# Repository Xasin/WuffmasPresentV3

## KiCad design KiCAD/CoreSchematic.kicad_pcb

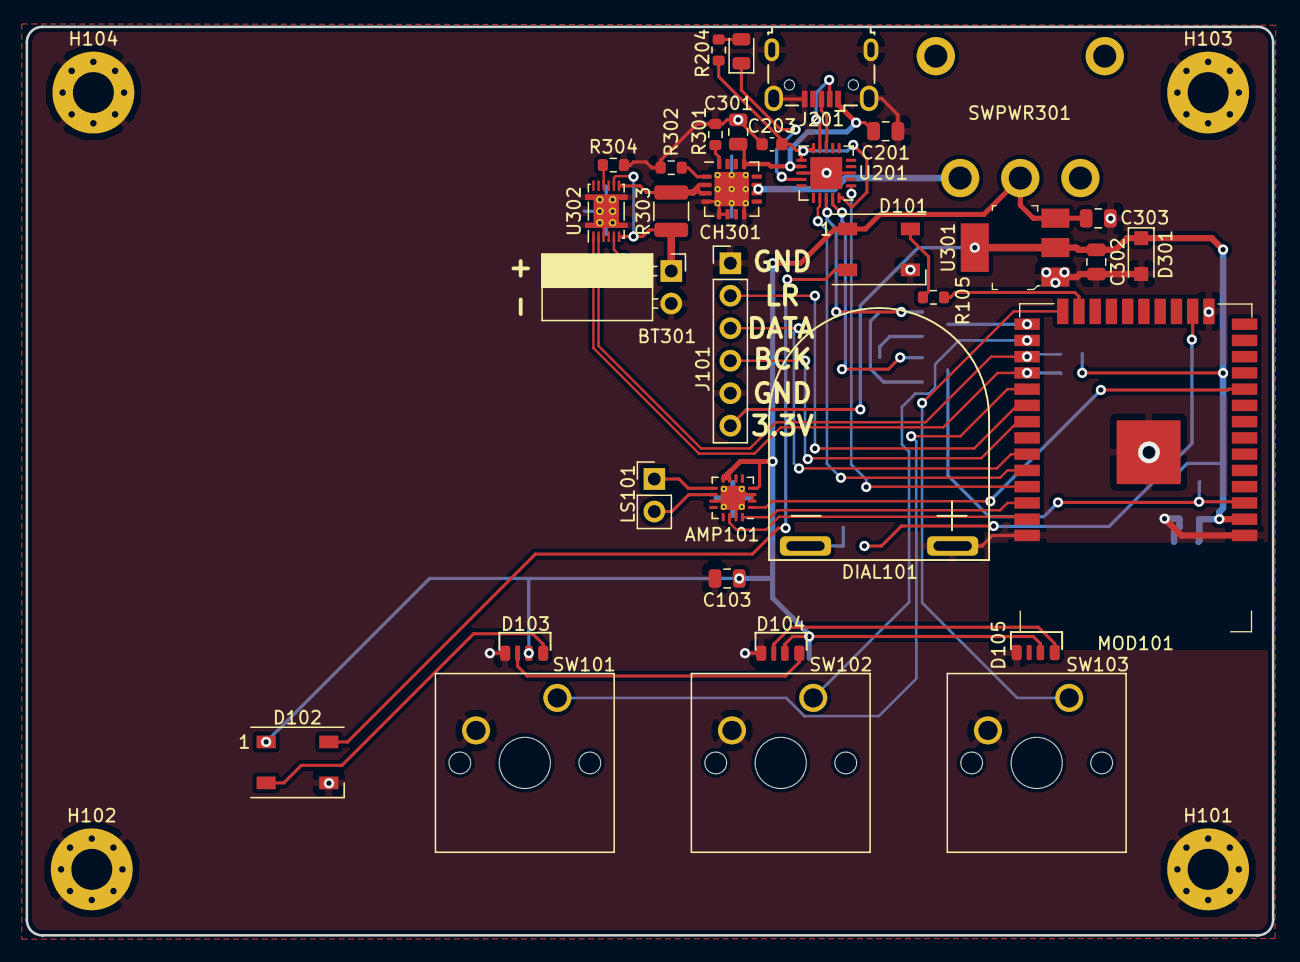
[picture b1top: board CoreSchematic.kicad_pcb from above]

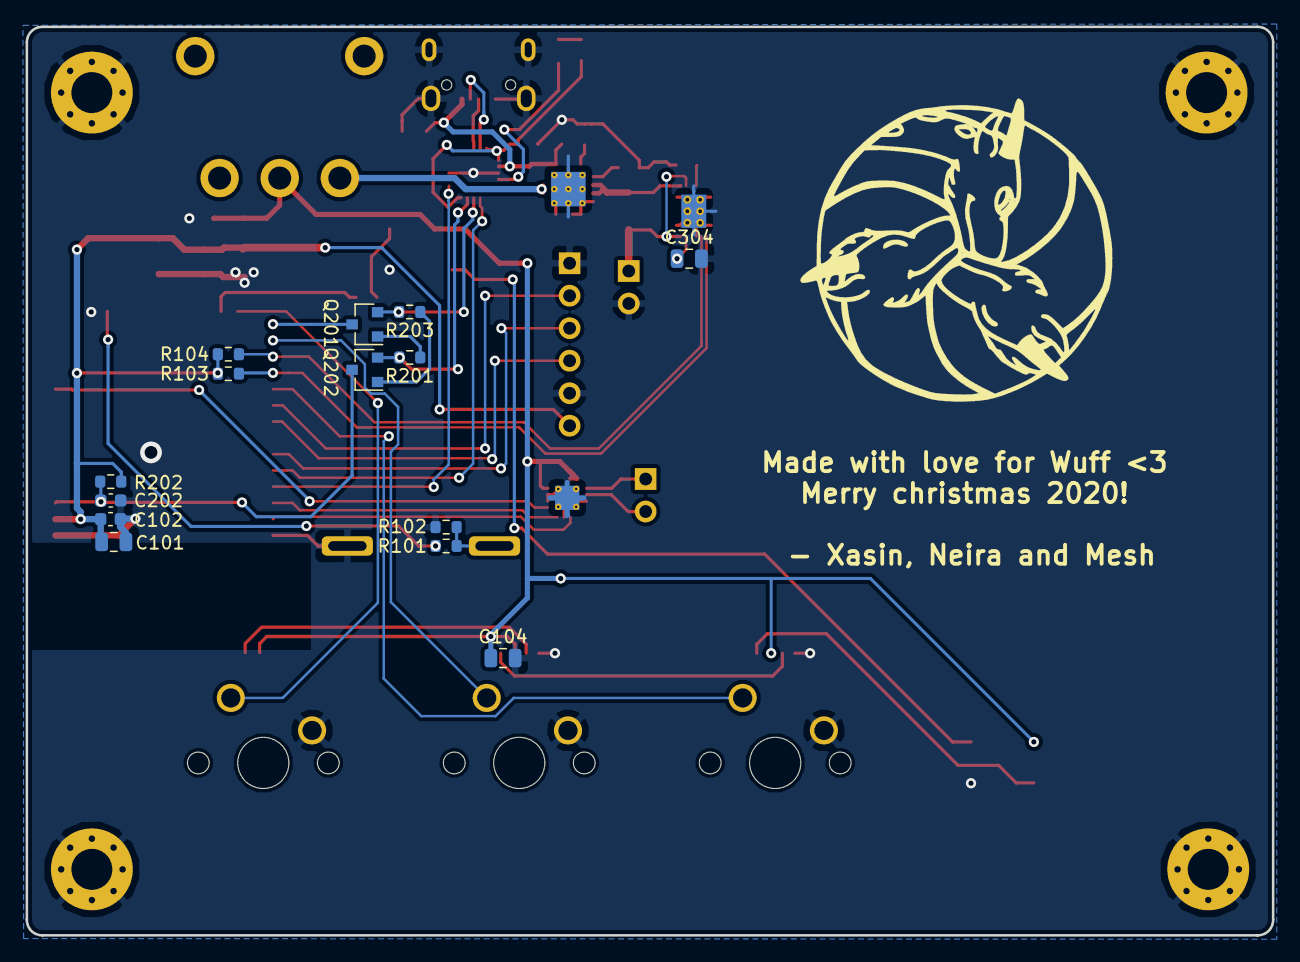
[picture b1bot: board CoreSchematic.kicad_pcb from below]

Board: 2 copper layers, 97.4 x 71.0 mm, 53 parts (15 on the bottom side), 45 nets.

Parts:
AMP101: MAX98357A; QFN-16-1EP_3x3mm_P0.5mm_EP1.9x1.9mm_ThermalVias
BT301: Battery_Cell; PinSocket_1x02_P2.54mm_Horizontal
C101, C103: C; C_0805_2012Metric
C102: 0.1uF; C_0603_1608Metric
C104, C301, C303: 1uF; C_0805_2012Metric
C201, C302: 10uF; C_0805_2012Metric
C202, C203: 100nF; C_0603_1608Metric
C304: 0.47uF; C_0805_2012Metric
CH301: BQ24232; Texas_S-PVQFN-N16_EP2.7x2.7mm_ThermalVias
D101, D102: WS2812B; LED_WS2812B_PLCC4_5.0x5.0mm_P3.2mm
D103, D104, D105: WS2812B; IN-PI42TAS
D301: D_Zener_ALT; D_SOD-123F
DIAL101: Motor_DC; VU_Meter_Flat
DUSB201: LED; LED_0805_2012Metric
H101, H102, H103, H104: MountingHole_Pad; MountingHole_3.2mm_M3_Pad_Via
J101: Conn_01x06_Female; PinHeader_1x06_P2.54mm_Vertical
J201: USB_B_Micro; USB_Micro-B_Wuerth_629105150521
LS101: Speaker; PinHeader_1x02_P2.54mm_Vertical
MOD101: ESP32-WROOM-32; ESP32-WROOM-32D
Q201, Q202: Q_NPN_BEC; SOT-23
R101, R102, R202, R301: R_Small; R_0603_1608Metric
R103, R104, R105, R201, R203, R302, R304: 10k; R_0603_1608Metric
R204: 220; R_0603_1608Metric
R303: 10mΩ; R_1210_3225Metric
SW101, SW102, SW103: SW_Push; SW_Cherry_MX_1.00u_PCB
SWPWR301: 500SSP1S1M6QEA; E-Switch_500_M6_SPDT
SYM101: SYM_Earth_Protective_Small; DragonIcon_25mm
U201: FT231XQ; QFN-20-1EP_4x4mm_P0.5mm_EP2.5x2.5mm
U301: AP2114H-3_3TRG1; SOT-223
U302: BQ27441-G1; Texas_S-PDSO-N12

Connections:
+3V3: C101.1, C102.1, C302.1, D301.1, J101.6, MOD101.2, R103.1, R104.1, R202.1, U301.2, U301.4
+BATT: AMP101.4, AMP101.7, AMP101.8, C103.1, C104.1, C303.1, D101.1, D102.1, D103.1, D104.1, D105.1, SWPWR301.2, U301.3
/BTN0_PLAY: MOD101.24, SW103.1
/BTN1_REC: MOD101.26, SW102.1
/BTN2_STOP: MOD101.29, SW101.1
/BTN_LEDS: D101.2, D102.4
/DIAL_PWM: MOD101.16, R101.1
/E>U: MOD101.35, U201.1
/GPIO0: MOD101.25, Q201.3
/MIC_BCK: J101.4, MOD101.31
/MIC_DATA: J101.3, MOD101.33
/MIC_LR: J101.2, MOD101.30
/OUT_BCK: AMP101.16, MOD101.36
/OUT_DATA: AMP101.1, MOD101.10
/OUT_LR: AMP101.14, MOD101.37
/Power/BSense-: BT301.1, R303.2, U302.6, U302.8
/Power/B_Raw+: CH301.2, CH301.3, R303.1, U302.7
/RESET: C202.1, MOD101.3, Q202.3, R202.2
/SPEAKER_LED: D101.4, R105.1
/U>E: MOD101.34, U201.17
/USB Con + Prog/+5V_USB: C201.2, C301.1, CH301.13, J201.1, U201.12
/USB Con + Prog/DTR: Q201.2, R203.2, U201.18
/USB Con + Prog/RTS: Q202.2, R201.2, U201.19
/USB Con + Prog/USB3.3: C203.2, R204.1, U201.10, U201.11, U201.20
/USB Con + Prog/USB+: J201.3, U201.8
/USB Con + Prog/USB-: J201.2, U201.9
GND: AMP101.2, AMP101.3, AMP101.11, AMP101.15, AMP101.17, BT301.2, C101.2, C102.2, C103.2, C104.2, C201.1, C202.2, C203.1, C301.2, C302.2, C303.2, C304.2, CH301.4, CH301.5, CH301.6, CH301.8, CH301.17, D101.3, D102.3, D103.3, D104.3, D105.3, D301.2, DIAL101.2, H101.1, H102.1, H103.1, H104.1, J101.1, J101.5, J201.5, J201.6, MOD101.1, MOD101.15, MOD101.38, MOD101.39, R102.2, R301.2, R302.2, R304.2, SW101.2, SW102.2, SW103.2, U201.3, U201.13, U201.21, U301.1, U302.3, U302.13
unnamed: AMP101.9, LS101.1
unnamed: AMP101.10, LS101.2
unnamed: C304.1, U302.5
unnamed: CH301.1, R302.1
unnamed: CH301.10, CH301.11, SWPWR301.1
unnamed: CH301.16, R301.1
unnamed: D102.2, D103.4
unnamed: D103.2, D104.4
unnamed: D104.2, D105.4
unnamed: DIAL101.1, R101.2, R102.1
unnamed: DUSB201.1, U201.14
unnamed: DUSB201.2, R204.2
unnamed: MOD101.23, R105.2
unnamed: Q201.1, R201.1
unnamed: Q202.1, R203.1
unnamed: R304.1, U302.10
SCL: MOD101.27, R104.2, U302.2
SDA: MOD101.28, R103.2, U302.1

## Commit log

2020-10-07 Begin work on nompy KiCAD schematic
2020-10-30 Add more content :D
2020-12-03 Add gitmodules and extend KiCAD schematics
2020-12-04 Upgrade to next XasCode commit
2020-12-04 Include the main ESP32 project
2020-12-10 Add first basic components for audio playback management
2020-12-16 Add a bit of Dial PWM
2020-12-16 Include the I2S Microphone
2020-12-23 Add wrapper class to help with handling the WuffCorder
2020-12-29 Make a rough first 'echo' system
2020-12-29 Forgot to update this
2021-01-05 Add first simple versin of a server (non-configurable for now)
2021-01-06 Added smol henlo message
2021-05-25 This shouldn't really be here anyways
2022-01-08 Add extra files
